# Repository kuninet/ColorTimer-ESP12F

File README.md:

# カラータイマー(ESP-12F版)

## 概要
* LED2つでカラータイマーを実現
* ESP-12Fで動作。
* IFTTTなどと連携してみたい

## 回路図
[回路図](image/ColorTimer-ESP12F.pdf)

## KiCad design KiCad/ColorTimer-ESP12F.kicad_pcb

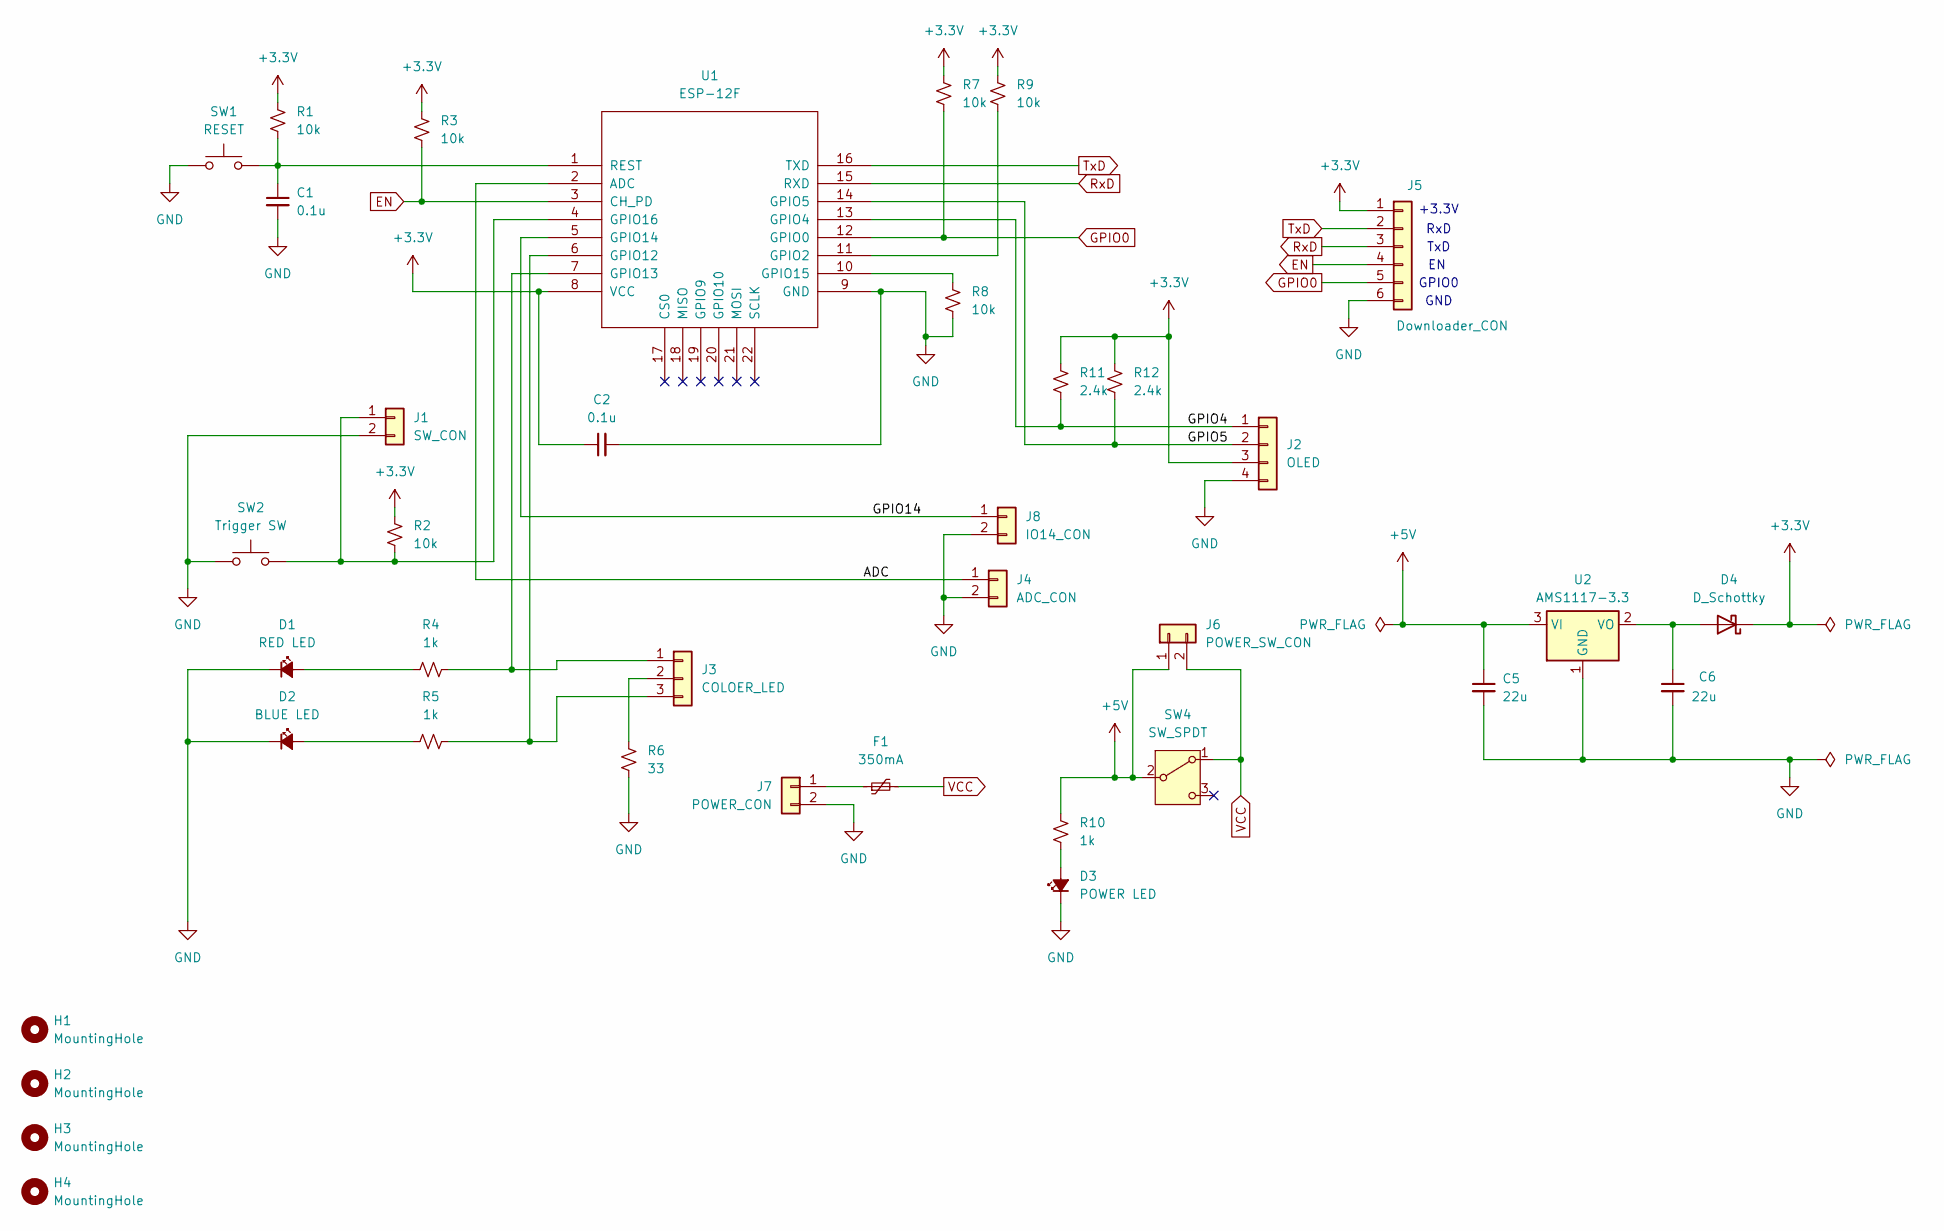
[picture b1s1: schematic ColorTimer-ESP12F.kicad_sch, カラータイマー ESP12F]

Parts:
C1, C2: 0.1u; C_0603_1608Metric_Pad1.08x0.95mm_HandSolder
C5, C6: 22u; C_0603_1608Metric_Pad1.08x0.95mm_HandSolder
D1: RED LED; LED_0603_1608Metric_Pad1.05x0.95mm_HandSolder
D2: BLUE LED; LED_0603_1608Metric_Pad1.05x0.95mm_HandSolder
D3: POWER LED; LED_0603_1608Metric_Pad1.05x0.95mm_HandSolder
D4: D_Schottky; D_SOD-123
F1: 350mA; Fuse_1206_3216Metric_Pad1.42x1.75mm_HandSolder
H1, H2, H3, H4: MountingHole; MountingHole_3.2mm_M3
J1: SW_CON; JST_XH_B2B-XH-A_1x02_P2.50mm_Vertical
J2: OLED; JST_XH_B4B-XH-A_1x04_P2.50mm_Vertical
J3: COLOER_LED; JST_XH_B3B-XH-A_1x03_P2.50mm_Vertical
J4: ADC_CON; JST_XH_B2B-XH-A_1x02_P2.50mm_Vertical
J5: Downloader_CON; PinSocket_1x06_P2.54mm_Vertical
J6: POWER_SW_CON; JST_XH_B2B-XH-A_1x02_P2.50mm_Vertical
J7: POWER_CON; JST_XH_B2B-XH-A_1x02_P2.50mm_Vertical
J8: IO14_CON; JST_XH_B2B-XH-A_1x02_P2.50mm_Vertical
R1, R2, R3, R7, R8, R9: 10k; R_0603_1608Metric_Pad0.98x0.95mm_HandSolder
R4, R5, R10: 1k; R_0603_1608Metric_Pad0.98x0.95mm_HandSolder
R6: 33; R_0603_1608Metric_Pad0.98x0.95mm_HandSolder
R11, R12: 2.4k; R_0603_1608Metric_Pad0.98x0.95mm_HandSolder
SW1: RESET; SW_Push_SPST_NO_Alps_SKRK
SW2: Trigger SW; SW_Push_SPST_NO_Alps_SKRK
SW4: SW_SPDT; PinSocket_1x03_P2.54mm_Vertical
U1: ESP-12F; ESP-12E_SMD
U2: AMS1117-3.3; SOT-223-3_TabPin2

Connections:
+3.3V: C2.1, D4.1 (K), J2.3, J5.1, R1.1, R2.1, R3.1, R7.1, R9.1, R11.1, R12.1, U1.8 (VCC)
+5V: C5.1, J6.1, R10.2, SW4.2 (B), U2.3 (VI)
/ADC: J4.1, U1.2 (ADC)
/GPIO4: J2.1, R11.2, U1.13 (GPIO4)
/GPIO5: J2.2, R12.2, U1.14 (GPIO5)
/GPIO14: J8.1, U1.5 (GPIO14)
EN: J5.4, R3.2, U1.3 (CH_PD)
GND: C1.2, C2.2, C5.2, C6.2, D1.1 (K), D2.1 (K), D3.1 (K), J1.2, J2.4, J4.2, J5.6, J7.2, J8.2, R6.1, R8.2, SW1.1, SW2.1, U1.9 (GND), U2.1 (GND)
GPIO0: J5.5, R7.2, U1.12 (GPIO0)
unnamed: D1.2 (A), R4.1
unnamed: D2.2 (A), R5.1
unnamed: D3.2 (A), R10.1
unnamed: C6.1, D4.2 (A), U2.2 (VO)
unnamed: J1.1, R2.2, SW2.2, U1.4 (GPIO16)
unnamed: J3.1, R4.2, U1.7 (GPIO13)
unnamed: J3.2, R6.2
unnamed: J3.3, R5.2, U1.6 (GPIO12)
unnamed: F1.1, J7.1
unnamed: R9.2, U1.11 (GPIO2)
unnamed: R8.1, U1.10 (GPIO15)
unnamed: C1.1, R1.2, SW1.2, U1.1 (REST)
RxD: J5.3, U1.15 (RXD)
TxD: J5.2, U1.16 (TXD)
VCC: F1.2, J6.2, SW4.1 (A)

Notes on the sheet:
+3.3V
GND
RxD
TxD
GPIO0

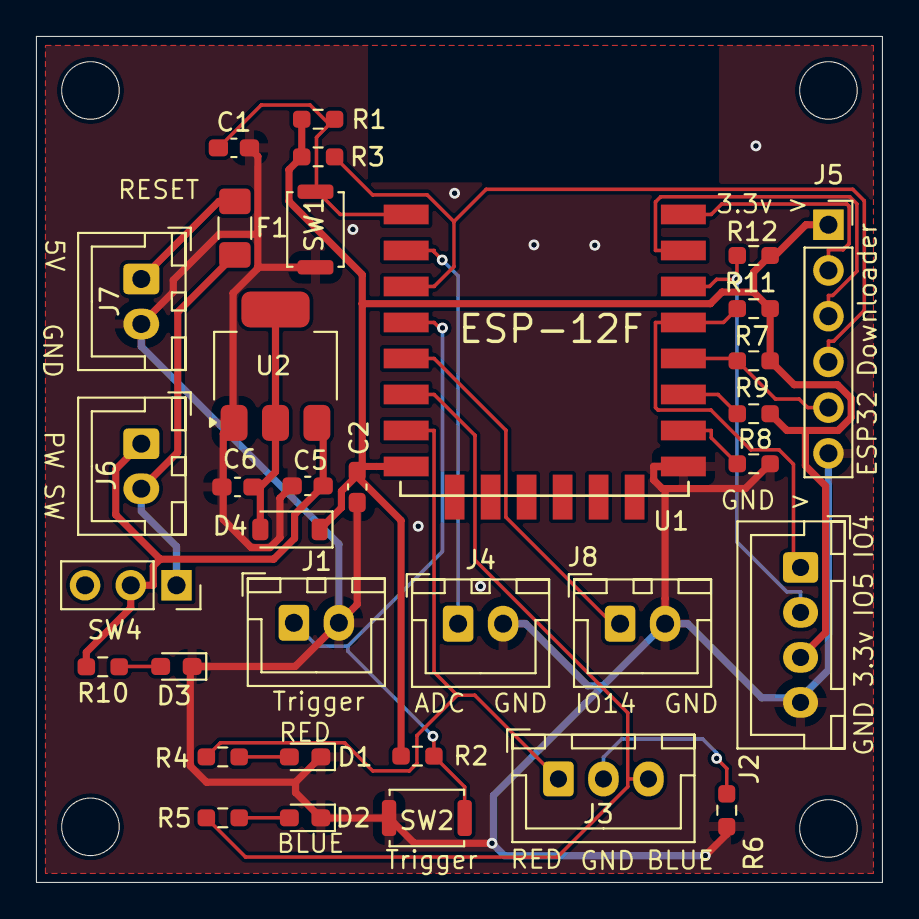
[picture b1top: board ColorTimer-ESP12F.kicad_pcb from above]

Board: 2 copper layers, 47.0 x 47.0 mm, 38 parts (0 on the bottom side), 24 nets.

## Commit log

2025-04-27 init
2025-04-27 回路図ひき始め
2025-04-27 回路図、パターン暫定版
2025-04-30 自動書き込み回路追加
2025-05-04 CH340K USBシリアル追加
2025-05-04 LED配線変更
2025-05-04 部品の関連付けなど
2025-05-05 コンデンサ等調整、AE-USB^MICRO-Bフットプリント追加
2025-05-08 回路間違い修正 & ガーバー出力
2025-05-11 微修正、ガーバー再出力
2025-05-25 ColorTimerプログラム 作成
2025-05-26 表面実装部品版 作成開始
2025-06-01 REV2 表面実装部品版 ガーバーデータ出力
2025-06-01 REV2 2色LEDのGNDに33Ω追加、ガーバー再出力 試作用
2025-11-29 REV1.1 回路検討
